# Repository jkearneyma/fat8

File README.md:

# fat8
A physically tiny, but fat in capability Intel 8008 SBC.  Smaller than a business card although quite a bit thicker.

This is not pure vintage design, rather its intent is to keep the flavor of one by pairing a real 8008 CPU with its maximum RAM footprint as a vehicle for running larger software like Scelbi's SCELBAL and GALAXY, emulators, and other fun projects.

- 8008 CPU running at ~ 50K instructions per second (500 KHz clock).
- 32KB of nonvolatile RAM (16KB addressable at a time)
- Connects to a PC as a USB serial terminal
- 3 input and 3 output ports available on an expansion connector
- Machine-level monitor program
- Prebuilt images for SCELBAL and GALAXY

[Hardware page](hardware/)\
[Software page](software/)\
[Tools page](tools/)

## Operation

1. Connect to USB
2. Open serial terminal program, for example minicom
3. Select the new port (probably /dev/ttyACM0) and set for to 2400 8N1
4. Press 'Reset' button
5. You should see the monitor prompt.  Press '?' for a list of commands.

## Licenses

Software and tools : [BSD-3-Clause](LICENSE.BSD-3-Clause)\
Hardware and CPLD programming : [CERN Open Hardware Licence Version 2 - Weakly Reciprocal](LICENSE.CERN-OHL-W-2.0)

SPDX-License-Identifier: BSD-3-Clause\
SPDX-License-Identifier: CERN Open Hardware Licence Version 2 - Weakly Reciprocal

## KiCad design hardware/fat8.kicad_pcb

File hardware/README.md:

# fat8 Hardware

The hardware is physically quite minimal but is still "discrete" in the sense that the 8008 CPU is supported by gate-level logic and an actual memory IC, not a microcontroller or FPGA pretending to be logic or memory.  The highest integration chip is actually the USB interface, which is actually an embedded PIC processor.  The only thing that device does is provide a clock signal and a TTL serial connection, however.

The memory IC is a ferro-magnetic RAM (FRAM), which is nonvolatile yet fast so it serves as both RAM and ROM in the design.

The "gate-level logic" is built in a programmable logic device.  It's relatively small (64 logic blocks), but that's big enough to implement the ~25 latches and 40+ gates needed to do all the state decoding, bus demultiplexing and other functions necessary.  The device is the (ex)Atmel ATF1504 CPLD.  It is old enough to have 5V I/O but new enough to be in-circuit (re)programmable using JTAG. Futhermore, it supports JTAG boundary scan, which allows us to download data into the FRAM by wiggling the I/O lines connected to it, which solves the bootstrap problem.

The [cpld/](../cpld/) folder contains the logic description for the CPLD, and the [tools/](../tools/) folder has the utilities needed to program the various devices.

The 8008 is a PMOS design, and requires a -9V supply (actually it requires a 14V supply and its logic signals are 9V-14V).  A small isolated DC-DC converter takes care of this.

This folder contains the schematic and board (Work In Progress) created in Kicad 9.

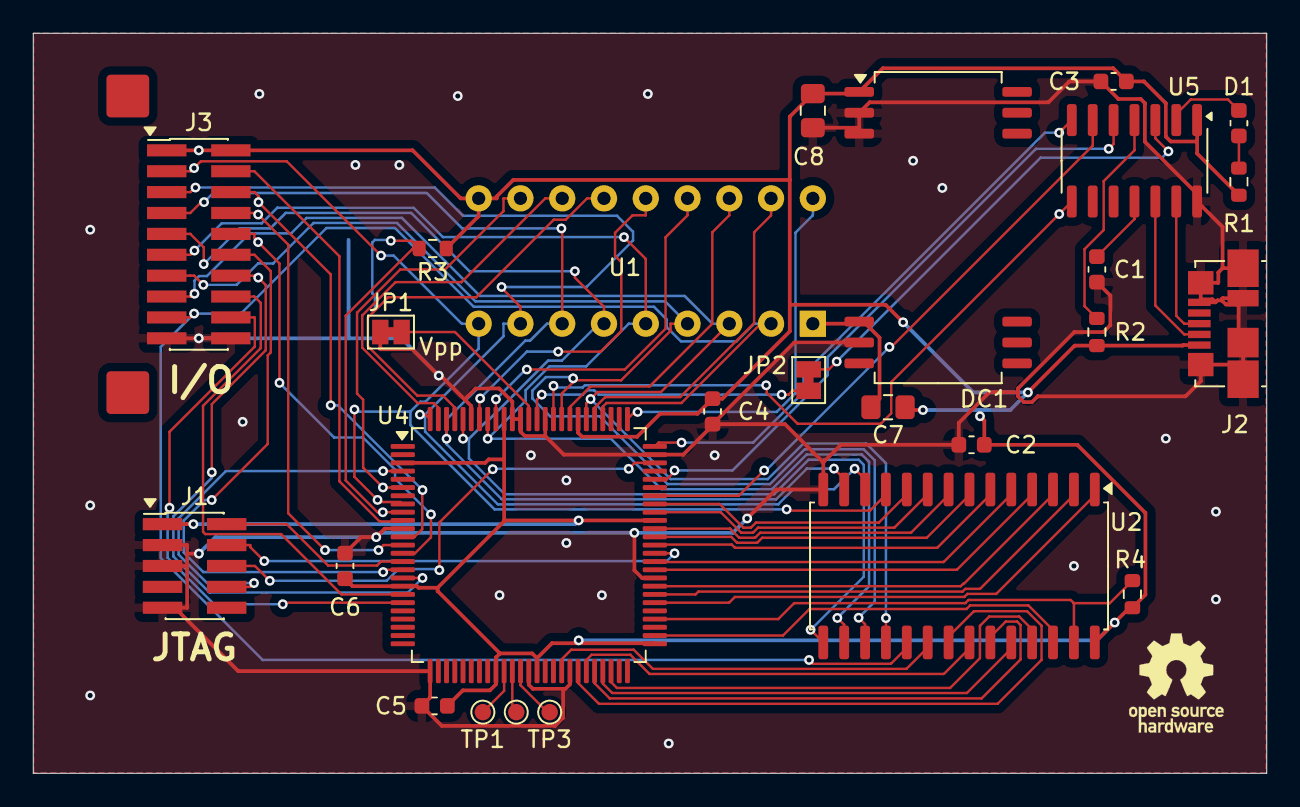
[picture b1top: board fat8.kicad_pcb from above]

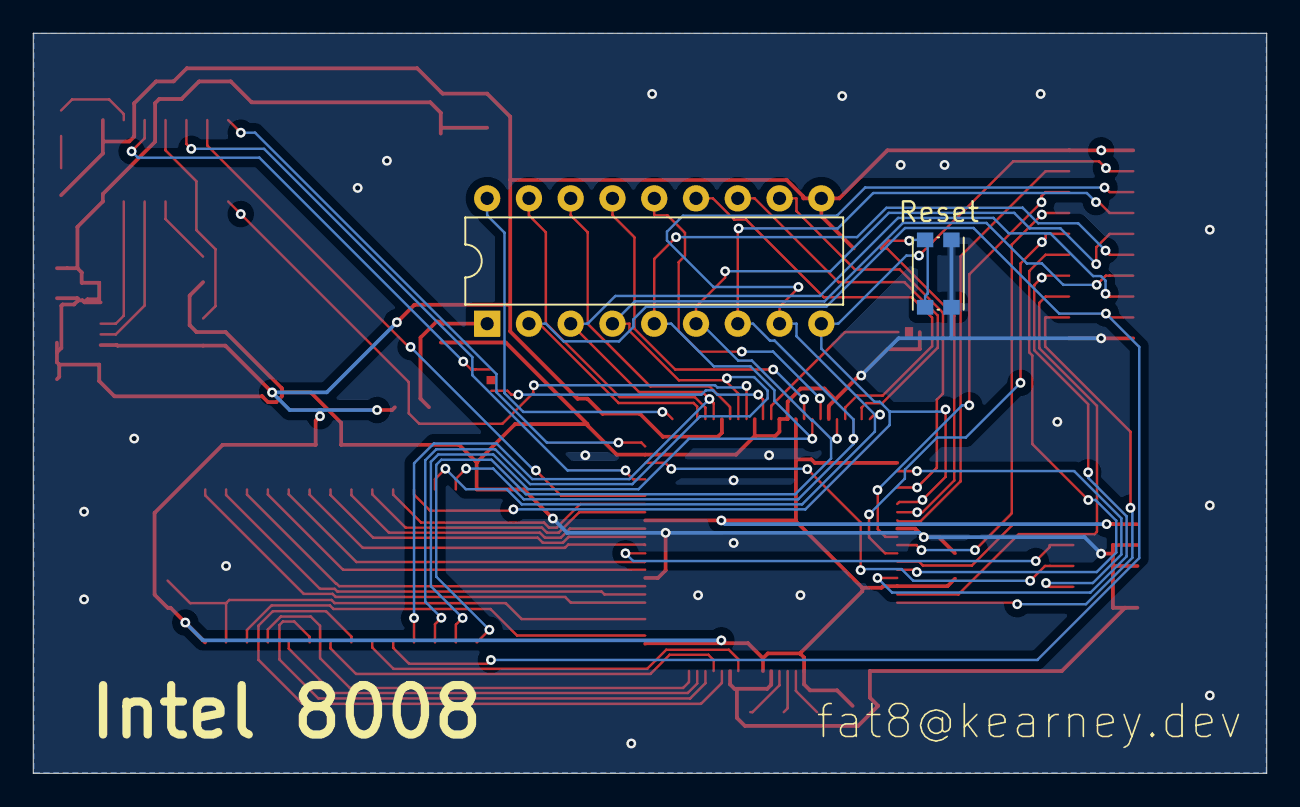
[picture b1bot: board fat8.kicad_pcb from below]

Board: 2 copper layers, 75.0 x 45.0 mm, 32 parts (2 on the bottom side), 66 nets.

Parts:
C1, C2, C3, C4, C5, C6: 0.1; C_0603_1608Metric
C7: 1.0; C_0805_2012Metric_Pad1.18x1.45mm_HandSolder
C8: 2.2 low ESR; C_0805_2012Metric_Pad1.18x1.45mm_HandSolder
D1: LED; C_0603_1608Metric
DC1: DCP020509U; SOIC-28W_7.5x18.7mm_P1.27mm
J1: Conn_ARM_JTAG_SWD_10; PinHeader_2x05_P1.27mm_Vertical_SMD
J2: USB_B_Micro; USB_Micro-B_Molex_47346-0001
J3: Conn_02x10_Row_Letter_First; PinHeader_2x10_P1.27mm_Vertical_SMD
JP1, JP2: SolderJumper_2_Bridged; SolderJumper-2_P1.3mm_Bridged_Pad1.0x1.5mm
MP1, MP2: MountingHole_2.2mm_M2_DIN965_Pad_TopOnly
R1: 1K; R_0603_1608Metric
R2, R3, R4: 10K; R_0603_1608Metric
SW1: KMR241GLFS; SW_Push_1P1T_NO_CK_KMR2
SYM1: OSHW-Logo_5.7x6mm_SilkScreen
SYM2, SYM3: c0931fb2-f178-4981-b6e2-5fc50c4e7324
TP1, TP2, TP3: TestPoint; TestPoint_Pad_D1.0mm
U1: C8008; DIP-18_W7.62mm
U2: FM1808B-SG; SOIC-28W_7.5x17.9mm_P1.27mm
U4: ATF1504ASL-25AU100; VQFP-100_14x14mm_P0.5mm
U5: MCP2221AxSL; SOIC-14_3.9x8.7mm_P1.27mm

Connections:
5V: C2.1, C3.1, C4.1, C5.1, C6.1, C7.1, C8.1, DC1.1 (+VS), J1.1 (VTref), J2.1 (VBUS), J3.a1, J3.b1, R1.1, R2.2, R3.1, R4.2, U1.10 (VCC), U2.28 (VDD), U4.3 (VCCIO_1), U4.18 (VCCIO_2), U4.34 (VCCIO_3), U4.39 (VCCINT_1), U4.51 (VCCIO_4), U4.66 (VCCIO_5), U4.82 (VCCIO_6), U4.91 (VCCINT_2), U5.1 (VDD)
-9V: C7.2, DC1.12 (-VOUT), U1.1 (VDD)
/D0: J3.a2, U1.9 (D0), U2.11 (DQ0), U4.8 (I/O_2)
/D1: J3.a3, U1.8 (D1), U2.12 (DQ1), U4.100 (I/O_57)
/D2: J3.a4, U1.7 (D2), U2.13 (DQ2), U4.98 (I/O_55)
/D3: J3.a5, U1.6 (D3), U2.15 (DQ3), U4.96 (I/O_53)
/D4: J3.a6, U1.5 (D4), U2.16 (DQ4), U4.93 (I/O_51)
/D5: J3.a7, U1.4 (D5), U2.17 (DQ5), U4.84 (I/O_49)
/D6: J3.a8, U1.3 (D6), U2.18 (DQ6), U4.81 (I/O_47)
/D7: J3.a9, U1.2 (D7), U2.19 (DQ7), U4.79 (I/O_45)
/FRAM_A0: U2.10 (A0), U4.68 (I/O_40)
/FRAM_A1: U2.9 (A1), U4.67 (I/O_39)
/FRAM_A2: U2.8 (A2), U4.65 (I/O_38)
/FRAM_A3: U2.7 (A3), U4.64 (I/O_37)
/FRAM_A4: U2.6 (A4), U4.63 (I/O_36)
/FRAM_A5: U2.5 (A5), U4.61 (I/O_35)
/FRAM_A6: U2.4 (A6), U4.60 (I/O_34)
/FRAM_A7: U2.3 (A7), U4.58 (I/O_33)
/FRAM_A8: U2.25 (A8), U4.48 (I/O_28)
/FRAM_A9: U2.24 (A9), U4.47 (I/O_27)
/FRAM_A10: U2.21 (A10), U4.44 (I/O_24)
/FRAM_A11: U2.23 (A11), U4.46 (I/O_26)
/FRAM_A12: U2.2 (A12), U4.57 (I/O_32)
/FRAM_A13: U2.26 (A13), U4.52 (I/O_29)
/FRAM_A14: U2.1 (A14), U4.56 (I/O_31)
/FRAM_CE/: U2.20 (~CE), U4.42 (I/O/PD2)
/FRAM_OE/: U2.22 (~OE), U4.45 (I/O_25)
/FRAM_WR/: R4.1, U2.27 (~WE), U4.54 (I/O_30)
/GP2: U4.75 (I/O_43), U5.7 (GP2)
/GP3: U4.85 (I/O/GCLK3), U5.8 (GP3)
/INT: U1.18 (INT), U4.76 (I/O_44)
/PI1: J3.b2, U4.10 (I/O_4)
/PI2: J3.b3, U4.12 (I/O/PD1)
/PI3: J3.b4, U4.13 (I/O_5)
/PO1: J3.b5, U4.14 (I/O_6)
/PO2: J3.b6, U4.16 (I/O_7)
/PO3: J3.b7, U4.17 (I/O_8)
/Ph1: U1.16 (ø1), U4.83 (I/O_48)
/Ph2: U1.15 (ø2), U4.92 (I/O_50)
/RDY: U1.17 (READY), U4.80 (I/O_46)
/RST: R3.2, SW1.2, U4.9 (I/O_3)
/RxD: U4.69 (I/O_41), U5.6 (UTx)
/S0: U1.13 (S0), U4.97 (I/O_54)
/S1: U1.12 (S1), U4.99 (I/O_56)
/S2: U1.11 (S2), U4.6 (I/O_1)
/ST1: J3.b8, U4.19 (I/O_9)
/ST3: J3.b9, U4.20 (I/O_10)
/SYNC: U1.14 (SYNC), U4.94 (I/O_52)
/TxD: U4.71 (I/O_42), U5.5 (URx)
/USB_CLK: JP2.2 (B), U4.87 (INPUT/GCLK1)
GND: C1.2, C2.2, C3.2, C4.2, C5.2, C6.2, C8.2, DC1.2 (-VS_1), DC1.3 (-VS_2), DC1.13 (+VOUT), J1.3 (GND), J1.5 (GND), J1.9 (GNDDetect), J2.5 (GND), J2.6 (Shield), J3.a10, J3.b10, JP1.1 (A), SW1.1, U2.14 (VSS), U4.11 (GND_1), U4.26 (GND_2), U4.38 (GND_3), U4.43 (GND_4), U4.59 (GND_5), U4.74 (GND_6), U4.86 (GND_7), U4.89 (INPUT/GCLR), U4.90 (INPUT/OE2/GCLK2), U4.95 (GND_8), U5.14 (VSS)
unnamed: D1.2 (A), R1.2
unnamed: D1.1 (K), U5.2 (GP0)
unnamed: J1.8 (NC/TDI), U4.4 (I/O/TDI)
unnamed: J1.4 (SWCLK/TCK), U4.62 (I/O/TCK)
unnamed: J1.2 (SWDIO/TMS), U4.15 (I/O/TMS)
unnamed: J1.6 (SWO/TDO), U4.73 (I/O/TDO)
unnamed: J2.3 (D+), U5.13 (D+)
unnamed: J2.2 (D-), U5.12 (D-)
unnamed: JP1.2 (B), U4.88 (INPUT/OE1)
unnamed: JP2.1 (A), U5.3 (GP1)
unnamed: TP1.1, U4.35 (I/O_19)
unnamed: TP2.1, U4.36 (I/O_20)
unnamed: TP3.1, U4.37 (I/O_21)
unnamed: C1.1, U5.11 (VUSB)
unnamed: R2.1, U5.4 (~RST)

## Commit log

2025-03-15 Initial upload
2025-04-24 checkpoint 20250424
